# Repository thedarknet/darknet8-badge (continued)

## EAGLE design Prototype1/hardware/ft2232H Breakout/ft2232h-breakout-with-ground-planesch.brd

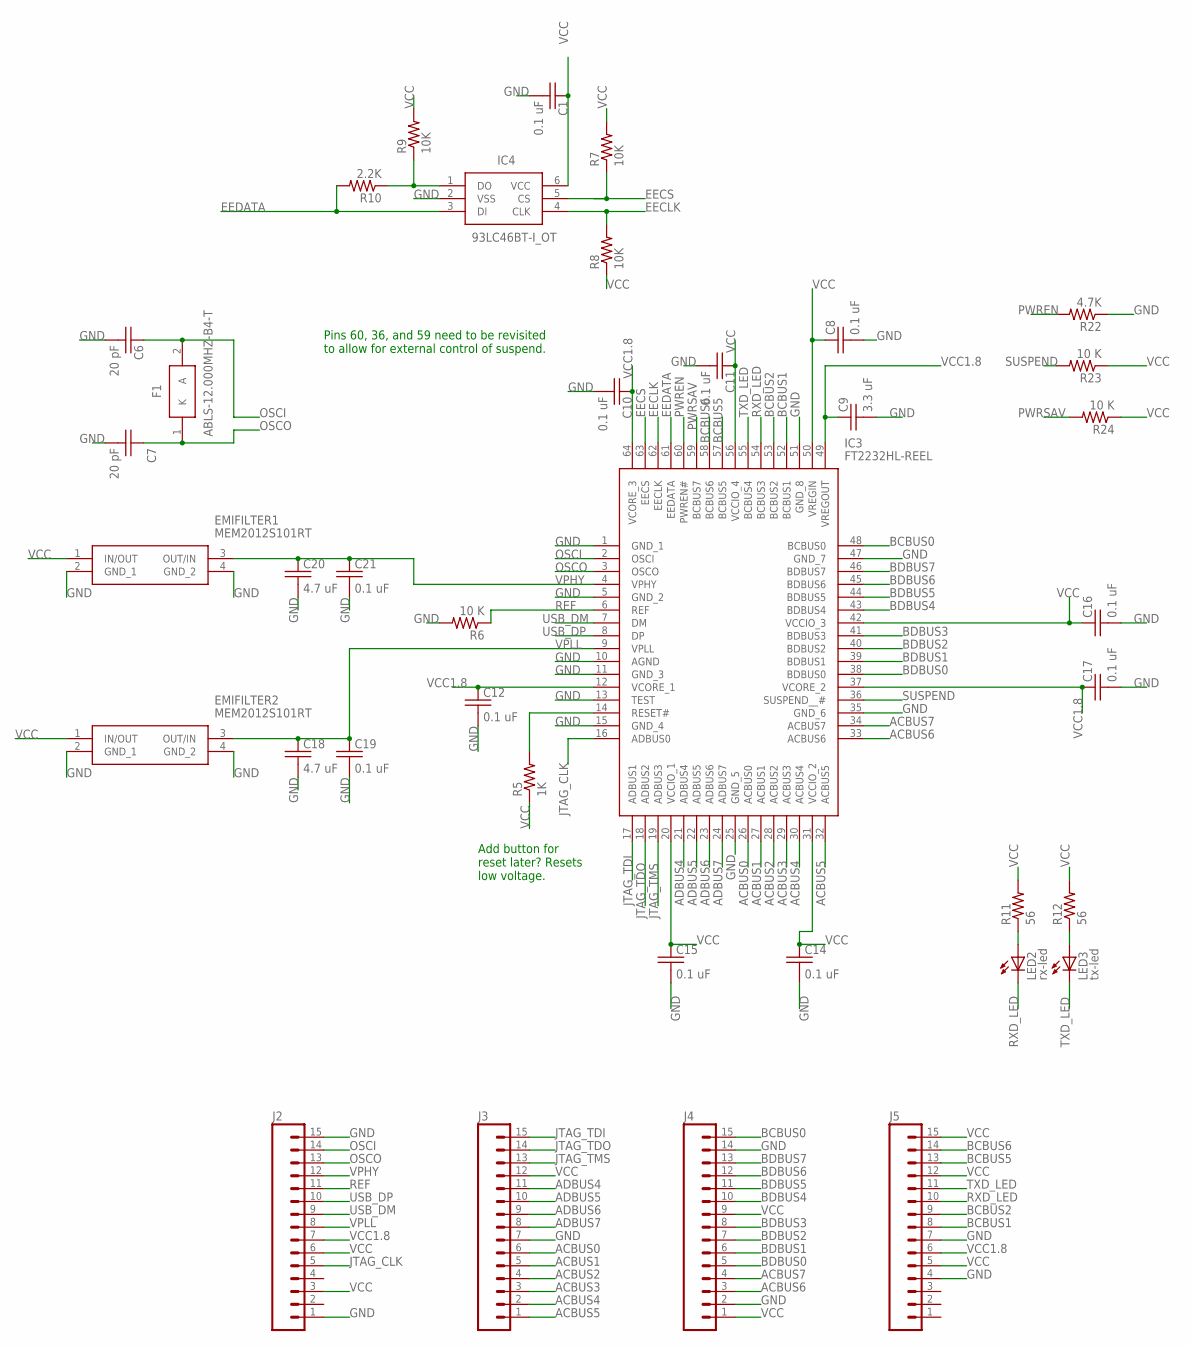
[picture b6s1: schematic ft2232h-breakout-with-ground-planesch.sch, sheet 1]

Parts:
C1, C8, C10, C11, C12, C14, C15, C16, C17, C19, C21: 0.1 uF; C0805
C6, C7: 20 pF; C0805
C9: 3.3 uF; C0805
C18, C20: 4.7 uF; C0805
EMIFILTER1, EMIFILTER2: MEM2012S101RT
F1: ABLS-12.000MHZ-B4-T; HC/49US-(AT49)_1
IC3: FT2232HL-REEL; QFP50P1200X1200X160-64N
IC4: 93LC46BT-I_OT; SOT95P270X145-6N
J2, J3, J4, J5: M15; 1X15
LED2: rx-led; LED3MM
LED3: tx-led; LED3MM
R5: 1K; 0805
R6, R23, R24: 10 K; 0805
R7, R8, R9: 10K; 0805
R10: 2.2K; 0805
R11, R12: 56; 0805
R22: 4.7K; 0805

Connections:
ACBUS0: IC3.26 (ACBUS0), J3.6
ACBUS1: IC3.27 (ACBUS1), J3.5
ACBUS2: IC3.28 (ACBUS2), J3.4
ACBUS3: IC3.29 (ACBUS3), J3.3
ACBUS4: IC3.30 (ACBUS4), J3.2
ACBUS5: IC3.32 (ACBUS5), J3.1
ACBUS6: IC3.33 (ACBUS6), J4.3
ACBUS7: IC3.34 (ACBUS7), J4.4
ADBUS4: IC3.21 (ADBUS4), J3.11
ADBUS5: IC3.22 (ADBUS5), J3.10
ADBUS6: IC3.23 (ADBUS6), J3.9
ADBUS7: IC3.24 (ADBUS7), J3.8
BCBUS0: IC3.48 (BCBUS0), J4.15
BCBUS1: IC3.52 (BCBUS1), J5.8
BCBUS2: IC3.53 (BCBUS2), J5.9
BCBUS5: IC3.57 (BCBUS5), J5.13
BCBUS6: IC3.58 (BCBUS6), J5.14
BDBUS0: IC3.38 (BDBUS0), J4.5
BDBUS1: IC3.39 (BDBUS1), J4.6
BDBUS2: IC3.40 (BDBUS2), J4.7
BDBUS3: IC3.41 (BDBUS3), J4.8
BDBUS4: IC3.43 (BDBUS4), J4.10
BDBUS5: IC3.44 (BDBUS5), J4.11
BDBUS6: IC3.45 (BDBUS6), J4.12
BDBUS7: IC3.46 (BDBUS7), J4.13
EECLK: IC3.62 (EECLK), IC4.4 (CLK), R8.2
EECS: IC3.63 (EECS), IC4.5 (CS), R7.1
EEDATA: IC3.61 (EEDATA), IC4.3 (DI), R10.2
GND: C1.2, C6.2, C7.2, C8.2, C9.2, C10.2, C11.2, C12.2, C14.2, C15.2, C16.2, C17.2, C18.2, C19.2, C20.2, C21.2, EMIFILTER1.2 (GND_1), EMIFILTER1.4 (GND_2), EMIFILTER2.2 (GND_1), EMIFILTER2.4 (GND_2), IC3.1 (GND_1), IC3.5 (GND_2), IC3.10 (AGND), IC3.11 (GND_3), IC3.13 (TEST), IC3.15 (GND_4), IC3.25 (GND_5), IC3.35 (GND_6), IC3.47 (GND_7), IC3.51 (GND_8), IC4.2 (VSS), J2.1, J2.15, J3.7, J4.2, J4.14, J5.4, J5.7, R6.2, R22.1; also elsewhere on the board
JTAG_CLK: IC3.16 (ADBUS0), J2.5
JTAG_TDI: IC3.17 (ADBUS1), J3.15
JTAG_TDO: IC3.18 (ADBUS2), J3.14
JTAG_TMS: IC3.19 (ADBUS3), J3.13
unnamed: IC3.14 (RESET#), R5.2
unnamed: IC4.1 (DO), R9.1, R10.1
unnamed: LED2.A, R11.1
unnamed: LED3.A, R12.1
OSCI: C6.1, F1.2 (A), IC3.2 (OSCI), J2.14
OSCO: C7.1, F1.1 (K), IC3.3 (OSCO), J2.13
PWREN: IC3.60 (PWREN#), R22.2
PWRSAV: IC3.59 (BCBUS7), R24.2
REF: IC3.6 (REF), J2.11, R6.1
RXD_LED: IC3.54 (BCBUS3), J5.10, LED2.K (C)
SUSPEND: IC3.36 (SUSPEND__#), R23.2
TXD_LED: IC3.55 (BCBUS4), J5.11, LED3.K (C)
USB_DM: IC3.7 (DM), J2.9; also elsewhere on the board
USB_DP: IC3.8 (DP), J2.10; also elsewhere on the board
VCC: C1.1, C8.1, C11.1, C14.1, C15.1, C16.1, EMIFILTER1.1 (IN/OUT), EMIFILTER2.1 (IN/OUT), IC3.20 (VCCIO_1), IC3.31 (VCCIO_2), IC3.42 (VCCIO_3), IC3.50 (VREGIN), IC3.56 (VCCIO_4), IC4.6 (VCC), J2.3, J2.6, J3.12, J4.1, J4.9, J5.5, J5.12, J5.15, R5.1, R7.2, R8.1, R9.2, R11.2, R12.2, R23.1, R24.1; also elsewhere on the board
VCC1.8: C9.1, C10.1, C12.1, C17.1, IC3.12 (VCORE_1), IC3.37 (VCORE_2), IC3.49 (VREGOUT), IC3.64 (VCORE_3), J2.7, J5.6
VPHY: C20.1, C21.1, EMIFILTER1.3 (OUT/IN), IC3.4 (VPHY), J2.12
VPLL: C18.1, C19.1, EMIFILTER2.3 (OUT/IN), IC3.9 (VPLL), J2.8

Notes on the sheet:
Add button for reset later? Resets low voltage.
Pins 60, 36, and 59 need to be revisited to allow for external control of suspend.

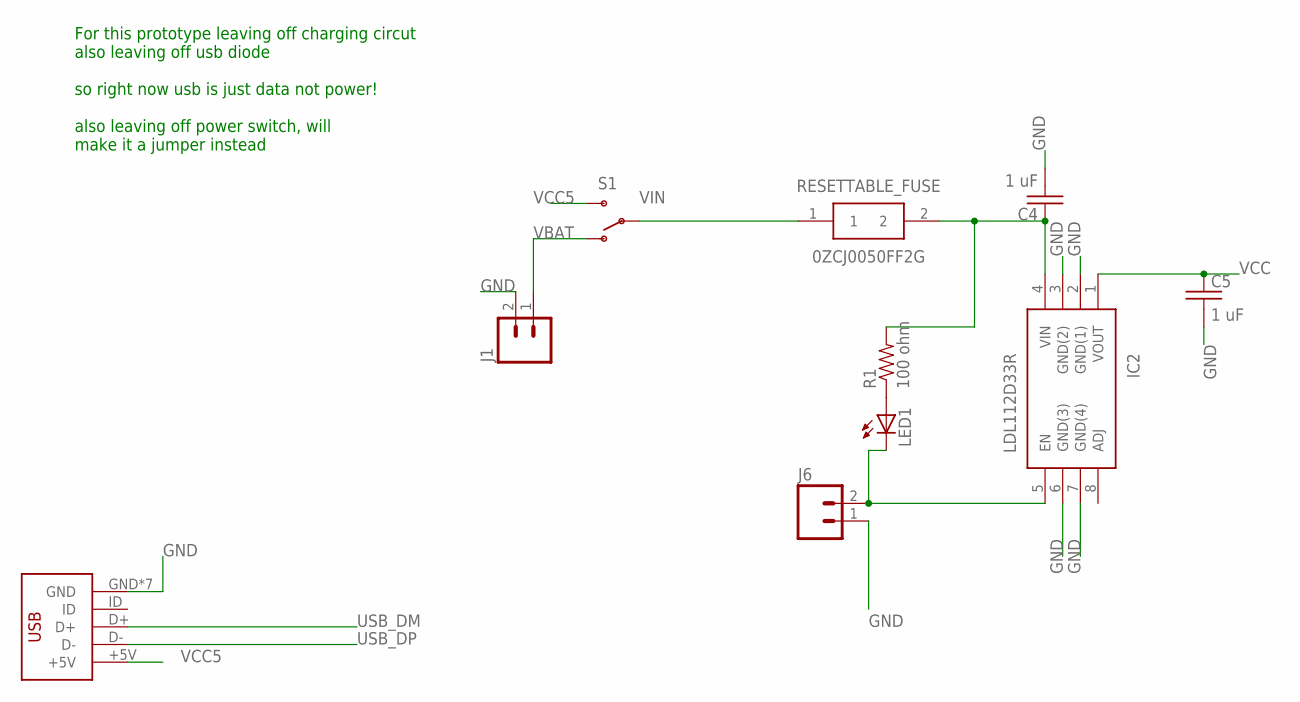
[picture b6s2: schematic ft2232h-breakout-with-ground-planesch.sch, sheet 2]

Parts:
C4, C5: 1 uF; C0805
IC2: LDL112D33R; SOIC127P600X175-8N
J1, J6: M02PTH; 1X02
LED1: LED3MM
R1: 100 ohm; AXIAL-0.3-KIT
RESETTABLE_FUSE: 0ZCJ0050FF2G; FUSC3216X55N
S1: SWITCH-SPSTPTH; SWITCH-SPDT
U$2: DX4R005JJ2DX4R005JJ2; DX4R005JJ2

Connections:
GND: C4.2, C5.2, IC2.2 (GND(1)), IC2.3 (GND(2)), IC2.6 (GND(3)), IC2.7 (GND(4)), J1.2, J6.1, U$2.GND, U$2.P$6 (GND), U$2.P$7 (GND), U$2.P$8 (GND), U$2.P$9 (GND), U$2.P$10 (GND), U$2.P$11 (GND); also elsewhere on the board
unnamed: LED1.A, R1.P$1 (1)
unnamed: C4.1, IC2.4 (VIN), R1.P$2 (2), RESETTABLE_FUSE.2
unnamed: IC2.5 (EN), J6.2, LED1.K (C)
USB_DM: U$2.D+; also elsewhere on the board
USB_DP: U$2.D-; also elsewhere on the board
VBAT: J1.1, S1.1 (O)
VCC: C5.1, IC2.1 (VOUT); also elsewhere on the board
VCC5: S1.3 (S), U$2.+5V
VIN: RESETTABLE_FUSE.1, S1.2

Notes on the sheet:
For this prototype leaving off charging circut also leaving off usb diode so right now usb is just data not power! also leaving off power switch, will make it a jumper instead

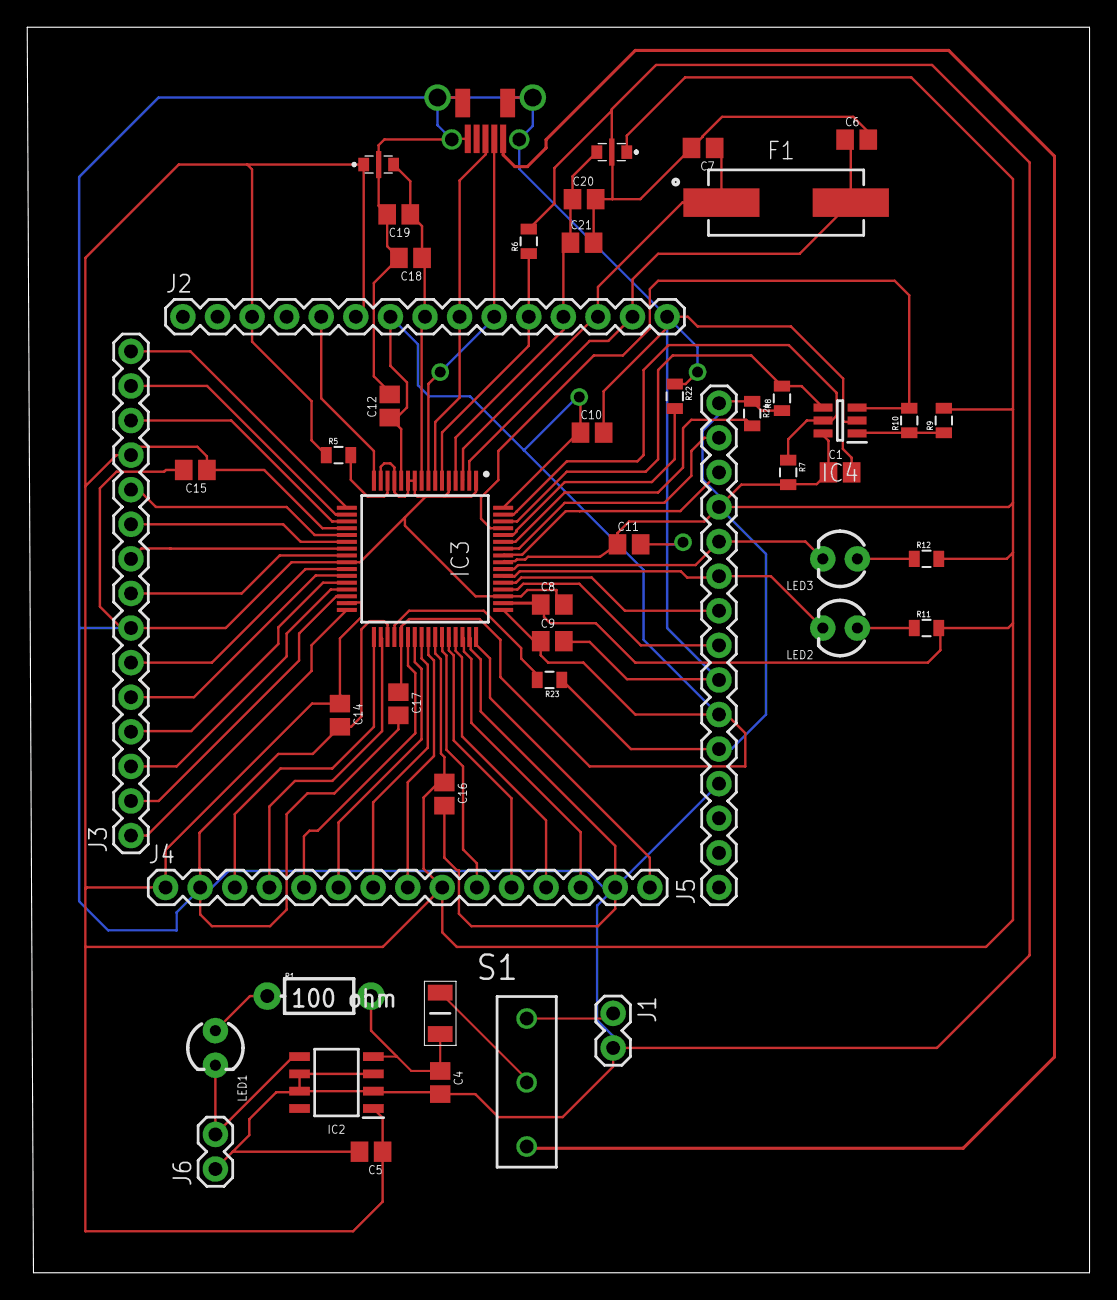
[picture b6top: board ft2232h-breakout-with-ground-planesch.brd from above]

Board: 2 copper layers, 78.0 x 91.5 mm, 48 parts (0 on the bottom side), 57 nets.

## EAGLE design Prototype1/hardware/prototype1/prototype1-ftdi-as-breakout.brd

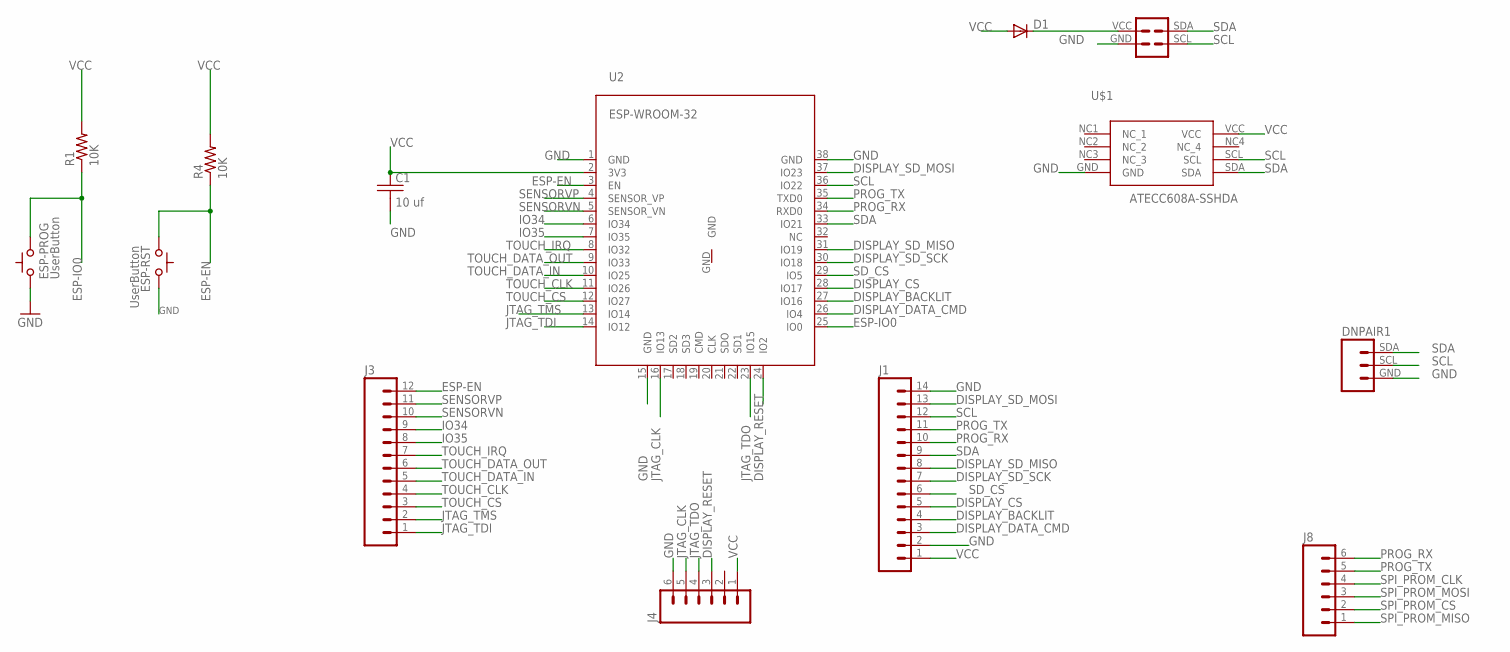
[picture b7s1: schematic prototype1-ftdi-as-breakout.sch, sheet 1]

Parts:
C1: 10 uf; C0805
D1: DIODESMA; SMA-DIODE
DNPAIR1: DARKNET_8_PAIR_CONNECTORPTH; 1X03
ESP-PROG: UserButton; TACTILE-2PIN-NARROW
ESP-RST: UserButton; TACTILE-2PIN-NARROW
J1: M14; 1X14
J3: M12PTH; 1X12
J4, J8: M06SILK_FEMALE_PTH; 1X06
R1, R4: 10K; 0805
SHITTY_ADDON: SAO1; DC26SHITTY_ADDON_CONNECTOR
U2: ESP-WROOM-32
U$1: ATECC608A-SSHDA; 8-SOIC

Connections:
DISPLAY_BACKLIT: J1.4, U2.27 (IO16)
DISPLAY_CS: J1.5, U2.28 (IO17)
DISPLAY_DATA_CMD: J1.3, U2.26 (IO4)
DISPLAY_RESET: J4.3, U2.24 (IO2)
DISPLAY_SD_MISO: J1.8, U2.31 (IO19)
DISPLAY_SD_MOSI: J1.13, U2.37 (IO23)
DISPLAY_SD_SCK: J1.7, U2.30 (IO18)
ESP-EN: ESP-RST.P$2 (C), J3.12, R4.1, U2.3 (EN)
ESP-IO0: ESP-PROG.P$1 (A), R1.1, U2.25 (IO0)
GND: C1.2, DNPAIR1.GND, ESP-PROG.P$2 (C), ESP-RST.P$1 (A), J1.2, J1.14, J4.6, SHITTY_ADDON.GND, U2.1 (GND), U2.15 (GND), U2.38 (GND), U$1.GND; also elsewhere on the board
IO34: J3.9, U2.6 (IO34)
IO35: J3.8, U2.7 (IO35)
JTAG_CLK: J4.5, U2.16 (IO13)
JTAG_TDI: J3.1, U2.14 (IO12)
JTAG_TDO: J4.4, U2.23 (IO15)
JTAG_TMS: J3.2, U2.13 (IO14)
unnamed: D1.C, SHITTY_ADDON.VCC
PROG_RX: J1.10, J8.6, U2.34 (RXD0)
PROG_TX: J1.11, J8.5, U2.35 (TXD0)
SCL: DNPAIR1.SCL, J1.12, SHITTY_ADDON.SCL, U2.36 (IO22), U$1.SCL
SDA: DNPAIR1.SDA, J1.9, SHITTY_ADDON.SDA, U2.33 (IO21), U$1.SDA
SD_CS: J1.6, U2.29 (IO5)
SENSORVN: J3.10, U2.5 (SENSOR_VN)
SENSORVP: J3.11, U2.4 (SENSOR_VP)
SPI_PROM_CLK: J8.4; also elsewhere on the board
SPI_PROM_CS: J8.2; also elsewhere on the board
SPI_PROM_MISO: J8.1; also elsewhere on the board
SPI_PROM_MOSI: J8.3; also elsewhere on the board
TOUCH_CLK: J3.4, U2.11 (IO26)
TOUCH_CS: J3.3, U2.12 (IO27)
TOUCH_DATA_IN: J3.5, U2.10 (IO25)
TOUCH_DATA_OUT: J3.6, U2.9 (IO33)
TOUCH_IRQ: J3.7, U2.8 (IO32)
VCC: C1.1, D1.A, J1.1, J4.1, R1.2, R4.2, U2.2 (3V3), U$1.VCC; also elsewhere on the board

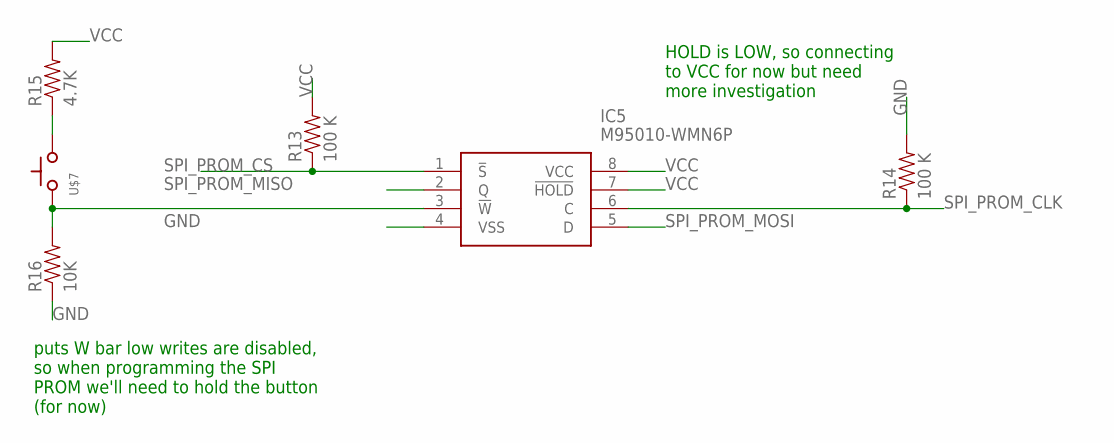
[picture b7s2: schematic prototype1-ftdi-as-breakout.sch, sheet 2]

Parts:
IC5: M95010-WMN6P; SOIC127P600X175-8N
R13, R14: 100 K; 0805
R15: 4.7K; 0805
R16: 10K; 0805
U$7: SWITCH_TACTILETACTILE-2PIN-NARROW; TACTILE-2PIN-NARROW

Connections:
GND: IC5.4 (VSS), R14.2, R16.1; also elsewhere on the board
unnamed: IC5.3 (!W), R16.2, U$7.P$2 (C)
unnamed: R15.1, U$7.P$1 (A)
SPI_PROM_CLK: IC5.6 (C), R14.1; also elsewhere on the board
SPI_PROM_CS: IC5.1 (!S), R13.1; also elsewhere on the board
SPI_PROM_MISO: IC5.2 (Q); also elsewhere on the board
SPI_PROM_MOSI: IC5.5 (D); also elsewhere on the board
VCC: IC5.7 (!HOLD), IC5.8 (VCC), R13.2, R15.2; also elsewhere on the board

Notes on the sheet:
HOLD is LOW, so connecting to VCC for now but need more investigation
puts W bar low writes are disabled, so when programming the SPI PROM we'll need to hold the button (for now)

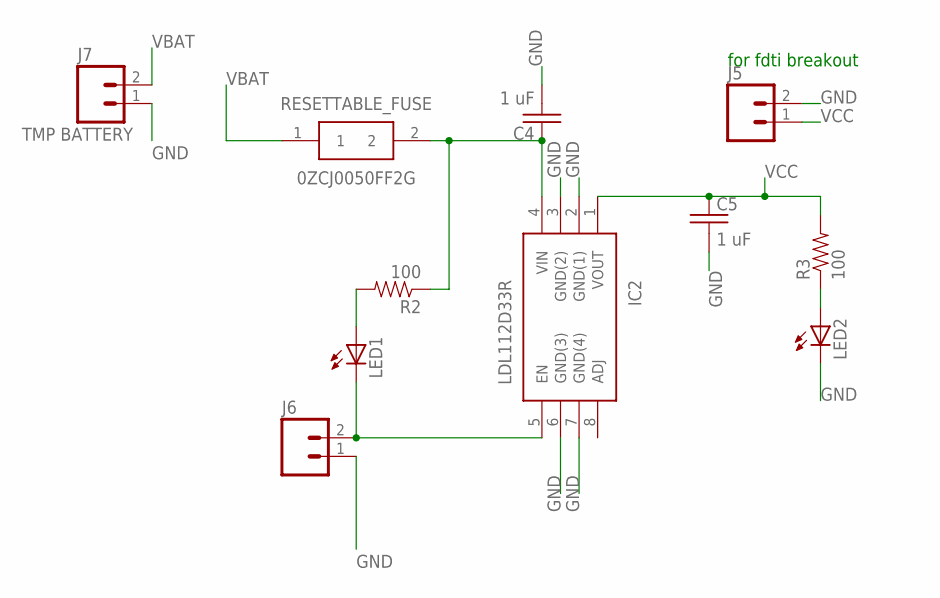
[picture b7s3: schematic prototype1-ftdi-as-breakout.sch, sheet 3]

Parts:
C4, C5: 1 uF; C0805
IC2: LDL112D33R; SOIC127P600X175-8N
J5, J6: M02PTH; 1X02
J7: TMP BATTERY; 1X02
LED1, LED2: LED3MM
R2, R3: 100; 0805
RESETTABLE_FUSE: 0ZCJ0050FF2G; FUSC3216X55N

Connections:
GND: C4.2, C5.2, IC2.2 (GND(1)), IC2.3 (GND(2)), IC2.6 (GND(3)), IC2.7 (GND(4)), J5.2, J6.1, J7.1, LED2.K (C); also elsewhere on the board
unnamed: C4.1, IC2.4 (VIN), R2.1, RESETTABLE_FUSE.2
unnamed: LED1.A, R2.2
unnamed: LED2.A, R3.1
unnamed: IC2.5 (EN), J6.2, LED1.K (C)
VBAT: J7.2, RESETTABLE_FUSE.1
VCC: C5.1, IC2.1 (VOUT), J5.1, R3.2; also elsewhere on the board

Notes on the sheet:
for fdti breakout

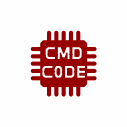
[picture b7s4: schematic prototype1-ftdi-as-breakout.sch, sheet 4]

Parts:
U$2: CMD_C0DE_LOGOCMD_CODE_LOGO_TOP_COPPER; CMD_C0DE_LOGO_TOP_COPPER

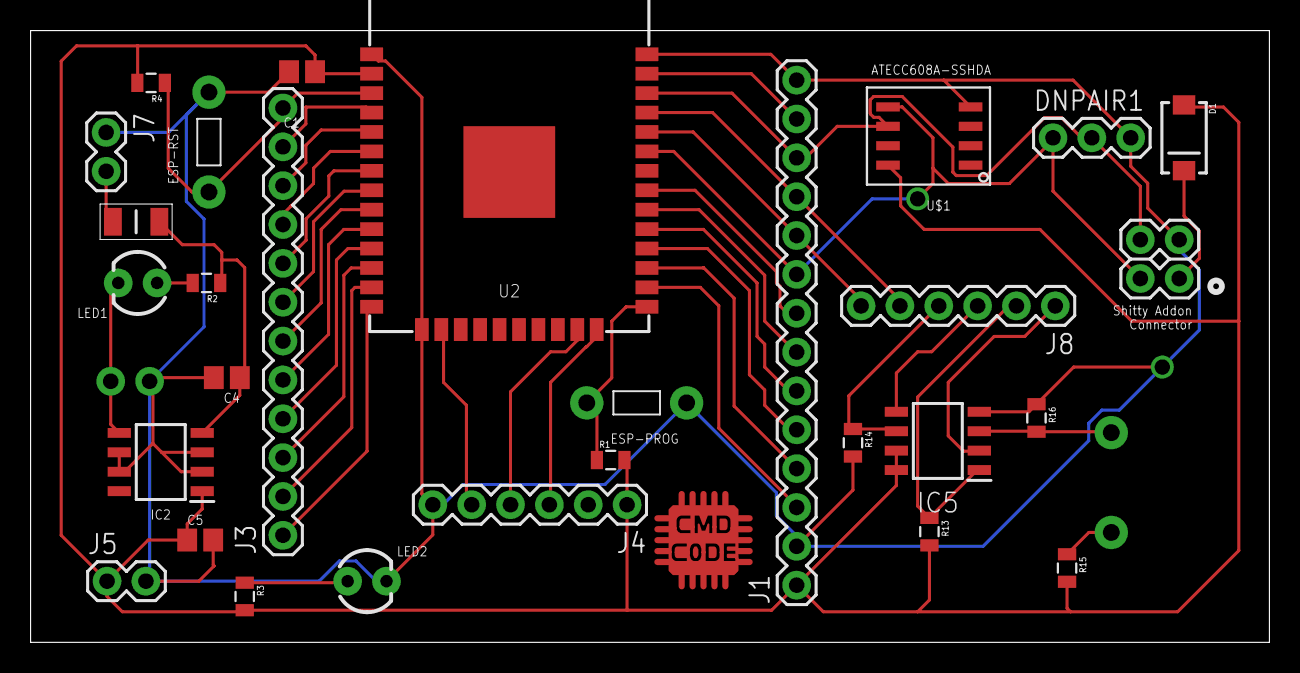
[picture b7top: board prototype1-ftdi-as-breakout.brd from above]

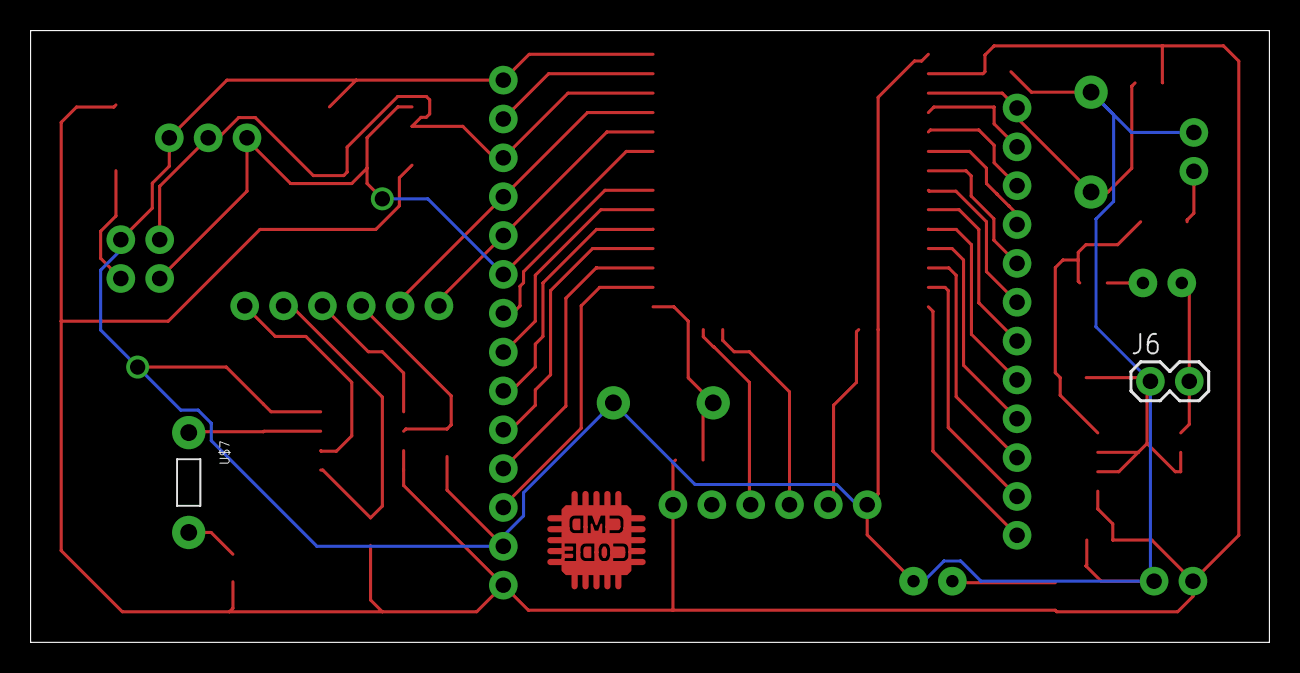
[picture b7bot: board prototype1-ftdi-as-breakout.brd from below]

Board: 2 copper layers, 81.0 x 40.0 mm, 32 parts (2 on the bottom side), 41 nets.

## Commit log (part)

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2018-12-30 early hardware prototype
2019-01-04 only FPGA left (I think) and a bunch of new reference material
2019-01-05 starting dev board layout
2019-01-07 initial prototype board design complete will use this one on bantam
2019-01-07 adding bantam plans as I'm getting very different milling times when plath is calced on my desktop vs my POS laptop I run the cnc with.
2019-01-15 vagrant working, container nearly working
2019-01-16 working build and flash, need tocheck debug yet
2019-01-21 breakout board without ftdi chip ready for bantam
2019-01-21 added logo and fixed drc error
2019-01-25 updated breakout board
2019-01-27 made outside traces a bit thicker
2019-01-27 a bit more room between traces
2019-02-04 adding voltera files for solder
2019-02-04 added bom
2019-02-17 adding docs
2019-02-22 started prototype 2 board
2019-02-23 prototype 2 schema done(?)
2019-02-23 fixed one more warning
2019-02-25 prototype 2 board design 'complete'
2019-02-26 removed top ground plane because bantam tools HATES that
2019-02-27 shorten board a bit so it fits on a 3x4 f4 board
2019-02-27 removing bad file location and fixing a missing ground
2019-02-27 adding voltera files back
2019-03-07 increased width of traces and tried a different package for slide switch
2019-03-14 fixed bug with center ground plane on esp32
2019-03-17 Dockerfile
2019-03-20 removed inputs to output pins....duh
2019-03-21 adding submodel
2019-03-30 moving over schema
2019-04-01 setting up dc27 repo for realz
2019-04-01 updating named main file
2019-04-01 dc27 board started for darknet 8
2019-04-02 adding basic layout dc27 badge
2019-04-03 started on changes to not charlie plex the leds
2019-04-04 top board farther, made a breakout board for new led driver
2019-04-05 basic layout nearly done
2019-04-05 adding apa102c
2019-04-07 start of Bluetooth Task code
2019-04-07 enable bluedroid
2019-04-07 bluetooth security startup, still need to do one last callback to hopefully make it work
2019-04-07 bluetooth code
2019-04-08 top board nearly complete
2019-04-12 nearly done
2019-04-13 fix initialization ording, pairing works with a pre-configured key
2019-04-13 start serial port code
2019-04-14 can boop serial profile from serial app on phone. echo not working yet
2019-04-14 what should be sent to pcbway
2019-04-20 comiles again
2019-04-27 Fixed artwork
    Fixed artwork which got mangled by Eagle's Push and shove routing
2019-04-27 Fixed copper ground planes
    Fixed copper ground planes
2019-04-28 Placeholder for game code
2019-04-28 Get BLE -> Game Task comms working. Turned on static allocation in menuconfig.
2019-04-28 Added BluetoothInteractions.drawio
2019-04-28 change name from serial game to game master and define contexts
2019-04-29 finish pong of ping
2019-04-29 minor changes
2019-04-29 add dc27
2019-05-05 removed apa 102s from top board swapped led driver for atmega4089 put on programming pads bottom board adding paring headers on bottom board added 1206 56 OHM resistors to each LED top board pulled o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
2019-05-05 moved pairing headers back so they don't stick out
2019-05-05 tweaked position of the led 7 and 8 to be at same Y as the right eye (+/- .1 mm) rerouted trace so it does not go between resistor on bottom board
2019-05-05 minor text changes
2019-05-06 moved JST down and to the left
2019-05-06 put hole in board just incase we have to mount battery to back
2019-05-12 started getting touch screen to work
2019-05-13 updated docker file to include a vimrc file
2019-05-16 adding docs and breakouts
2019-05-19 Update DC27-bottom.brd
    additional puzzle updates
2019-05-19 Add header to bluetooth message to allow sending large messages
    Could have messed with MTU size, but tests showed it to be not dependable
    This makes it such that you must use a pre-defined protocol to talk to the
    badge, since just using a serial client won't use our message format.
2019-05-19 finish ble in/out, start work on game master main menu
2019-05-20 adding FPA SAO
2019-05-21 compiles with lastest libesp library - ready to test touch
2019-05-21 logging
2019-05-23 nerd tree now installed in vim by default..working on youcompleteme
2019-05-25 finish up context switching, tested with locked and invalid context selections. Implemented a simple format string vulnerability quest to the Game Master as an example quest. Next we need to start im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
2019-05-25 Add start of example game: exploitable.
2019-05-26 Sample OTA Code. Binary size is too large :<
2019-05-26 fix OTATask::init
2019-05-26 OTA working, however the OTA library is massive (550k+)
2019-05-26 fix ota, the wifi and http configs have to be statically available
2019-05-26 Setup custom OTA partitions (1.3mb each), re-enable BLE And GameMaster for development. Leave OTA commented out for size purposes.
2019-05-26 Exploitable Game: create a level, make it easy to add more
2019-05-27 latest lib
2019-05-27 checking in sao changes
2019-05-27 change game task initialization to happen in dc27.cpp, and add a installGame call to the game_master.
2019-05-28 what should a simple test for the touch screen
2019-05-28 updated test
2019-05-29 updated sao
2019-05-30 deleted a bunch of unused code and touch screen is now working
2019-05-30 updated sao and docs
2019-06-02 starting work on main display
2019-06-02 Enable line of pwr switch is now what powers vbat on top board, so if you turnoff the badge top the top and the bottom board are off. :) Increased top board caps to 1206 from 0805
2019-06-03 tied pin 6 to cdone
2019-06-04 aligned with latest display code
2019-06-04 cleaned up silk screen top board
2019-06-05 updated silk screen so everything should be 'readable' 'squared off the usb area' so that its 1.2mm from the hole to the end of the board per data sheet.
2019-06-05 added cmdc0dez puzzle
2019-06-05 Added puzzle elemenets for Krux's Challenge.
    Added puzzle elemenets for Krux's Challenge. Cleaned up size/font/position for part labels
2019-06-06 moved vias
2019-06-06 Fixed the darknet logo, and made resistors pretty
2019-06-06 fixed my image
2019-06-16 display almost working
2019-06-17 final tweaks moved top board I2C to separate bus
2019-06-21 moved usb .15mm closer to edge per first pcb ask
2019-06-22 fixed i2c pull ups to be actual pull ups
2019-06-29 commit some old exploitable code i started on a while back
2019-06-30 reduce stack size of tasks, implement factory reset and verify OTA works
2019-06-30 cleanup libbt memory and flash usage
2019-06-30 turn OTA task on (doesn't reach out to anything)
2019-06-30 display ready to test
2019-07-02 WIP display
2019-07-03 closer on a working display
2019-07-03 almost working, color is just wrong
2019-07-04 display now works
2019-07-05 convert game selection from header data to characteristic selection, simplify the GameMessage format.
2019-07-06 store game unlocked status and exploitable game level in nvs. fix exploitable level 1.
2019-07-07 almost ready to start menuing logic
2019-07-10 add some xtensa assembly documentation for reference
2019-07-10 sample assembly
2019-07-10 input handling about 60% complete
2019-07-11 buttons now work, but somewhere I broke touch screen
2019-07-13 add a brainf*** interpreter and game with flags.
2019-07-13 move the string exploit to exploitable game and leave room for an 'unlock game code' section in the game_master
2019-07-13 adding all new menus
2019-07-13 add level selection, bad levels, and activate the secret level
2019-07-13 fix some exploitable prints
2019-07-13 'encrypt' flags, add an encryption script. Couldn't encrypt the one brainfuzz flag because of the way the challenge is written, so just leave it.
2019-07-13 fix exploitable level1 timeout. encode brainfuzz flag #2 on disk
2019-07-14 add 3d tic-tac-toe. almost works, bug in computer movement generation
2019-07-14 everything compiles but won't link
2019-07-14 tic-tac-toe works now. clean up some superfluous debug prints
2019-07-14 add better directions to ttt3d
2019-07-14 comments with decrypted flags
2019-07-14 stub out rest of exploitable quest, add another password guessing quest, add newline to gamemaster printer
2019-07-14 add very minor hint about the secret level
2019-07-14 menus are mostly on, starting to walk through each getting them to work
2019-07-15 badge pairing ping notes
2019-07-15 wifi iram optimization off
2019-07-15 removed address book and sao scan fixed game of life
2019-07-15 jam all the games into game_master.cpp
2019-07-15 move ota logic from a task to a menu, freeing up another 11k of memory.
2019-07-16 upping back buffer to 60% of display...yeah more memory back
2019-07-17 update for crashfix
2019-07-19 call off the last 2 levels planned for lack of time
2019-07-21 basic calibration stuff complete
2019-07-21 calibration now completely works next up to allow touch to navigate menus
2019-07-22 calibration works Test menu works main menu works with touch screen
2019-07-23 fixed the way components work so they are 'mostly' correct for the current esp32 make system (non-cmake based). but that meant removing <libesp/> from many includes but now we can include more than 1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
2019-07-26 basic crypto working
2019-07-27 start of pairing menu, most of the logic commented out, unable to test build because submodule is bad
2019-07-27 fix pairing menu build
2019-07-27 pushing to unfuck gourry?????
2019-07-28 contact store is close
2019-07-28 wifi, ota, and npc interactions tasks. extremely large commit.
2019-07-30 remove the wifi stuff until i can fix it appropriately
2019-07-30 devkit lcd pinout defines
2019-07-30 crytpo chip works initialize serial number gerneates device public/private key pair logs all config
2019-07-30 fix screen for wrover AND devkit
2019-07-30 off-by-one in onInit
2019-07-30 drop 1 ota partition, update sdkconfig for SPI ram
2019-07-30 fix wifi stuff, shuffle all these files around
2019-07-30 integrate SPIRAM into memory map model, increase resolution to 75%
2019-07-30 uncomment getWifiTask
2019-07-30 turn on wifi, reduce backbuffer to 50%, turn off SPIRAM support because ESP32-WROOM doesn't have it (ROVER Only). Add #GOURRY_DEVKIT define for pinouts and buttons
2019-07-31 turn off the wifi shhhtuff for now until we know the space and ram isn't killing it
2019-08-02 adding initial atmega4089 code
2019-08-03 i2c working via bus pirate
2019-08-03 bot board can talk to bottom board
2019-08-03 added a few new led dances
2019-08-04 wifi just about working adding memory debug
2019-08-04 memory debugging
2019-08-04 fixed crash bug
2019-08-04 get uart working for pairing menu, move all GPIO pin definitions to a central place
2019-08-04 setting flash to 8 MB
2019-08-04 fixed bug in horizontal light show
2019-08-04 basic pairing message passing without crypto logic
2019-08-05 add ble status (active/inactive) and passkey (random if active, 0 if inactive), to comm status menu.
2019-08-05 ability to choose BLE or WIFI (not actually implemented yet)
2019-08-05 fix random number generation
2019-08-05 fix communication settings menu, ble settings are no longer interactive
2019-08-05 honor wifi or bt
2019-08-05 move pairing uart initialization into pairing_menu.cpp
2019-08-05 fix storage->nvs issue
2019-08-05 small bug
2019-08-05 pairing scaffolding works, just requires crypto exchanges
2019-08-05 basics of drawing menu complete
2019-08-05 fixed badge info screen (mostly) vitual buttons in place for drawing
2019-08-05 OTA interaction from settings menu
2019-08-05 pairing code ...done?
2019-08-06 ota ap and password
2019-08-06 drawing mostly works. Fixed bug with display in badge info added timeout for screen saver added touch screen back on test Menu
2019-08-06 OTA works, menu is wonky, it is successful inconsistently due to what seems like memory or connection issues, greatest chance of success if you actually power-cycle the badge (turn it on and off)
2019-08-06 drawing menu now works
2019-08-06 game of life now uses atecc608a random number generator :)
2019-08-07 web server FINALLY working
2019-08-07 npc interaction 1/2 re-implemented
2019-08-07 fixed a bug with saving contacts the namespace was too long becasue 18 is indeed greater than 15
2019-08-08 fixed a bunch of UI bugs and made the print out of contacs better
2019-08-08 final top board firmware
    final top board
